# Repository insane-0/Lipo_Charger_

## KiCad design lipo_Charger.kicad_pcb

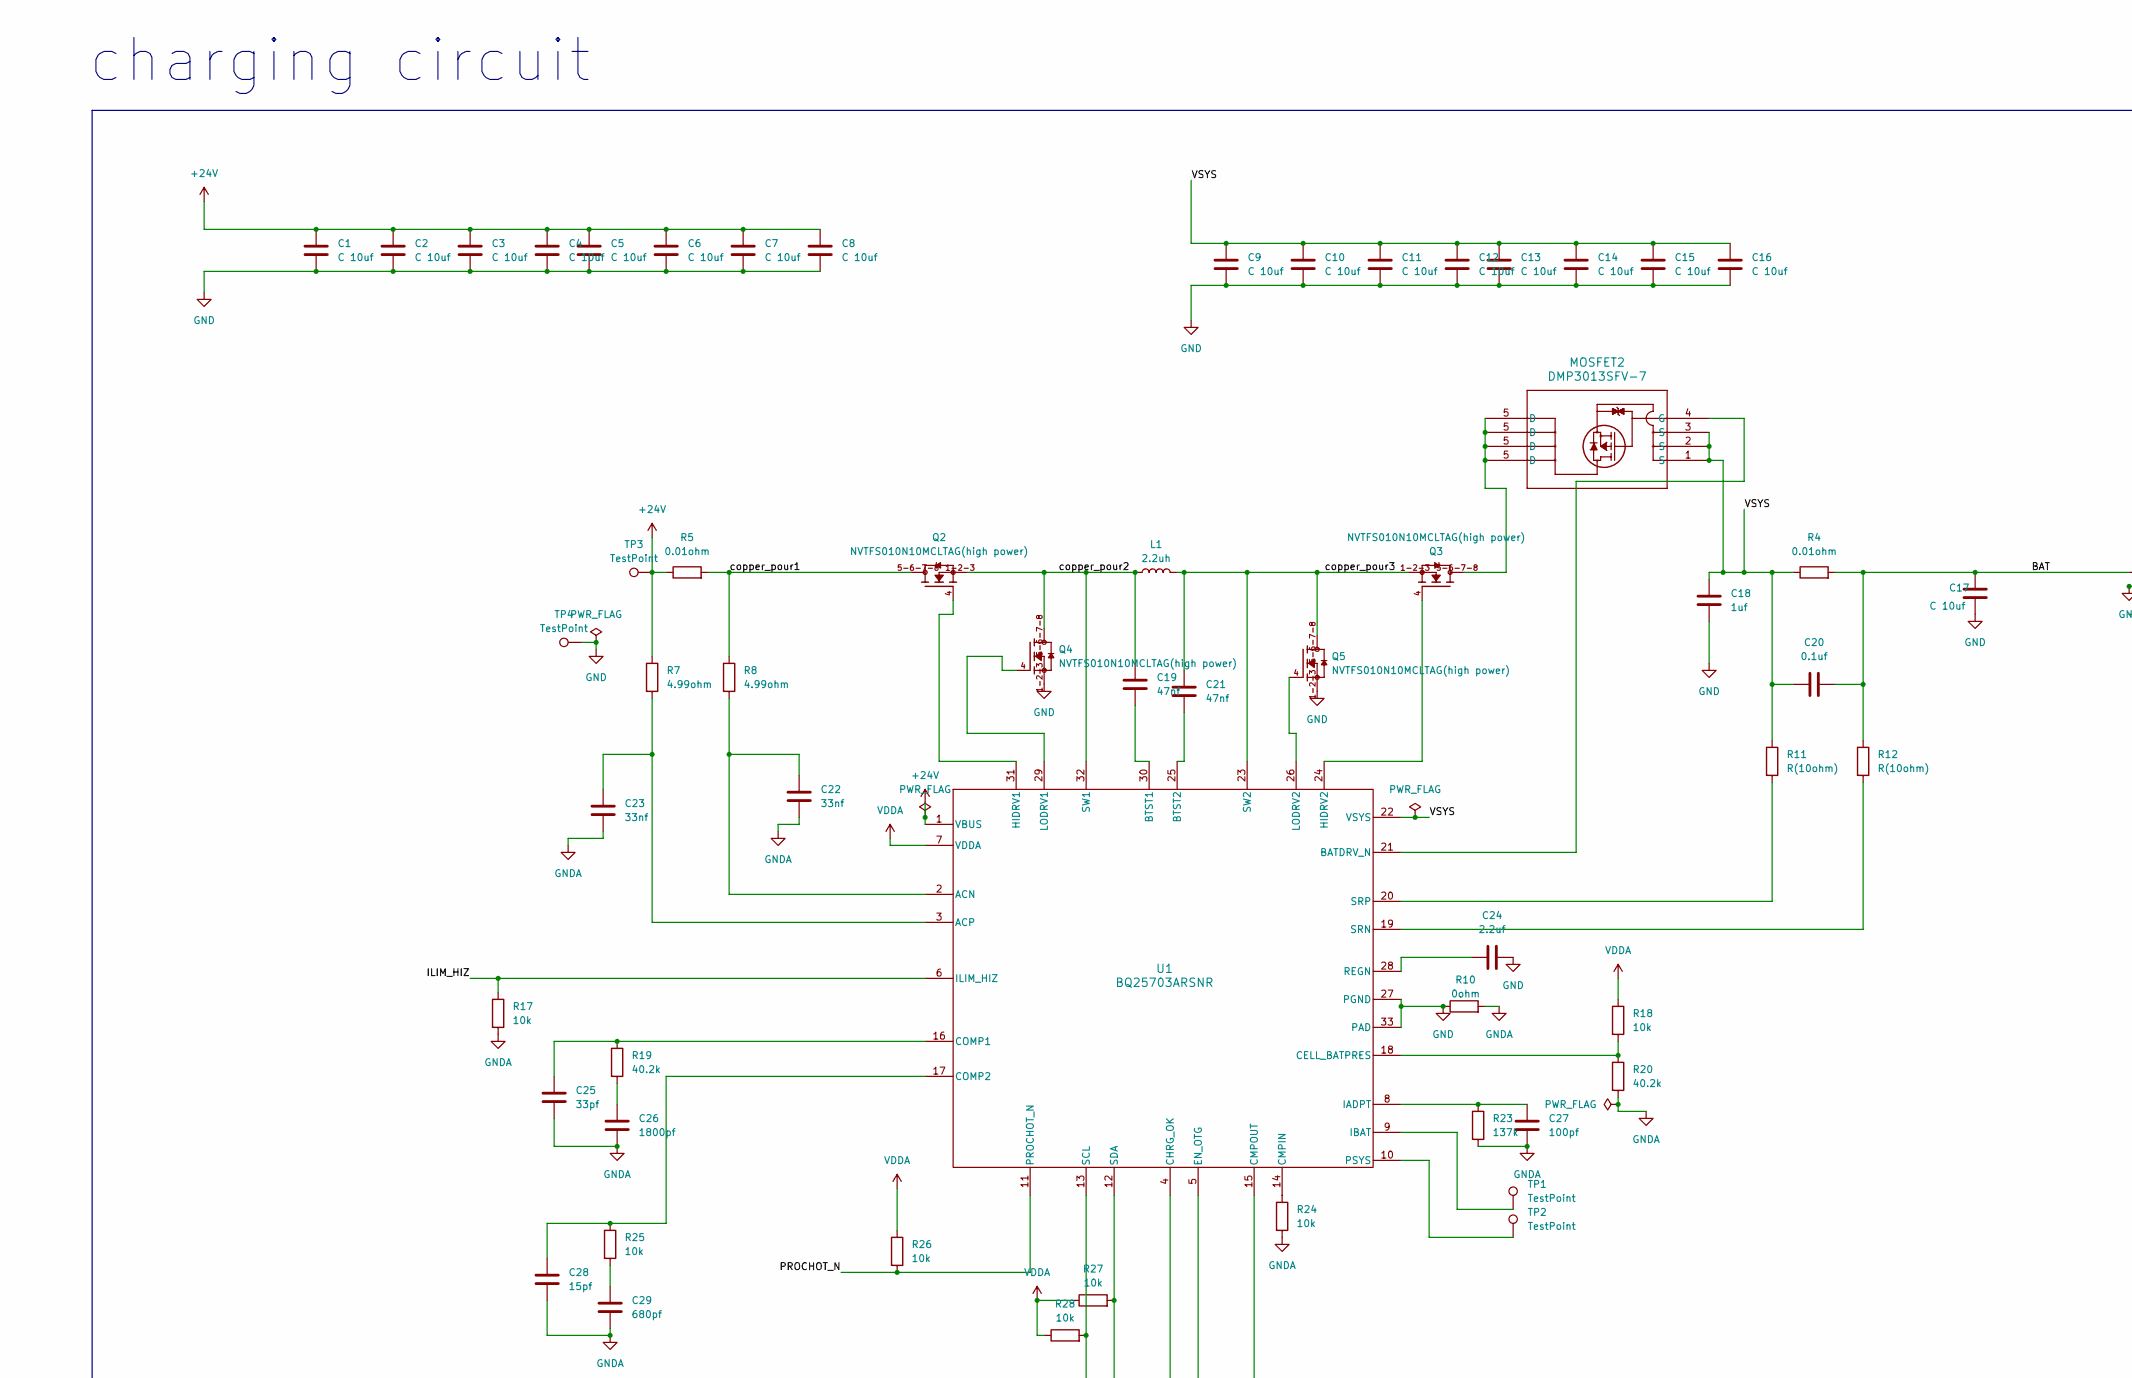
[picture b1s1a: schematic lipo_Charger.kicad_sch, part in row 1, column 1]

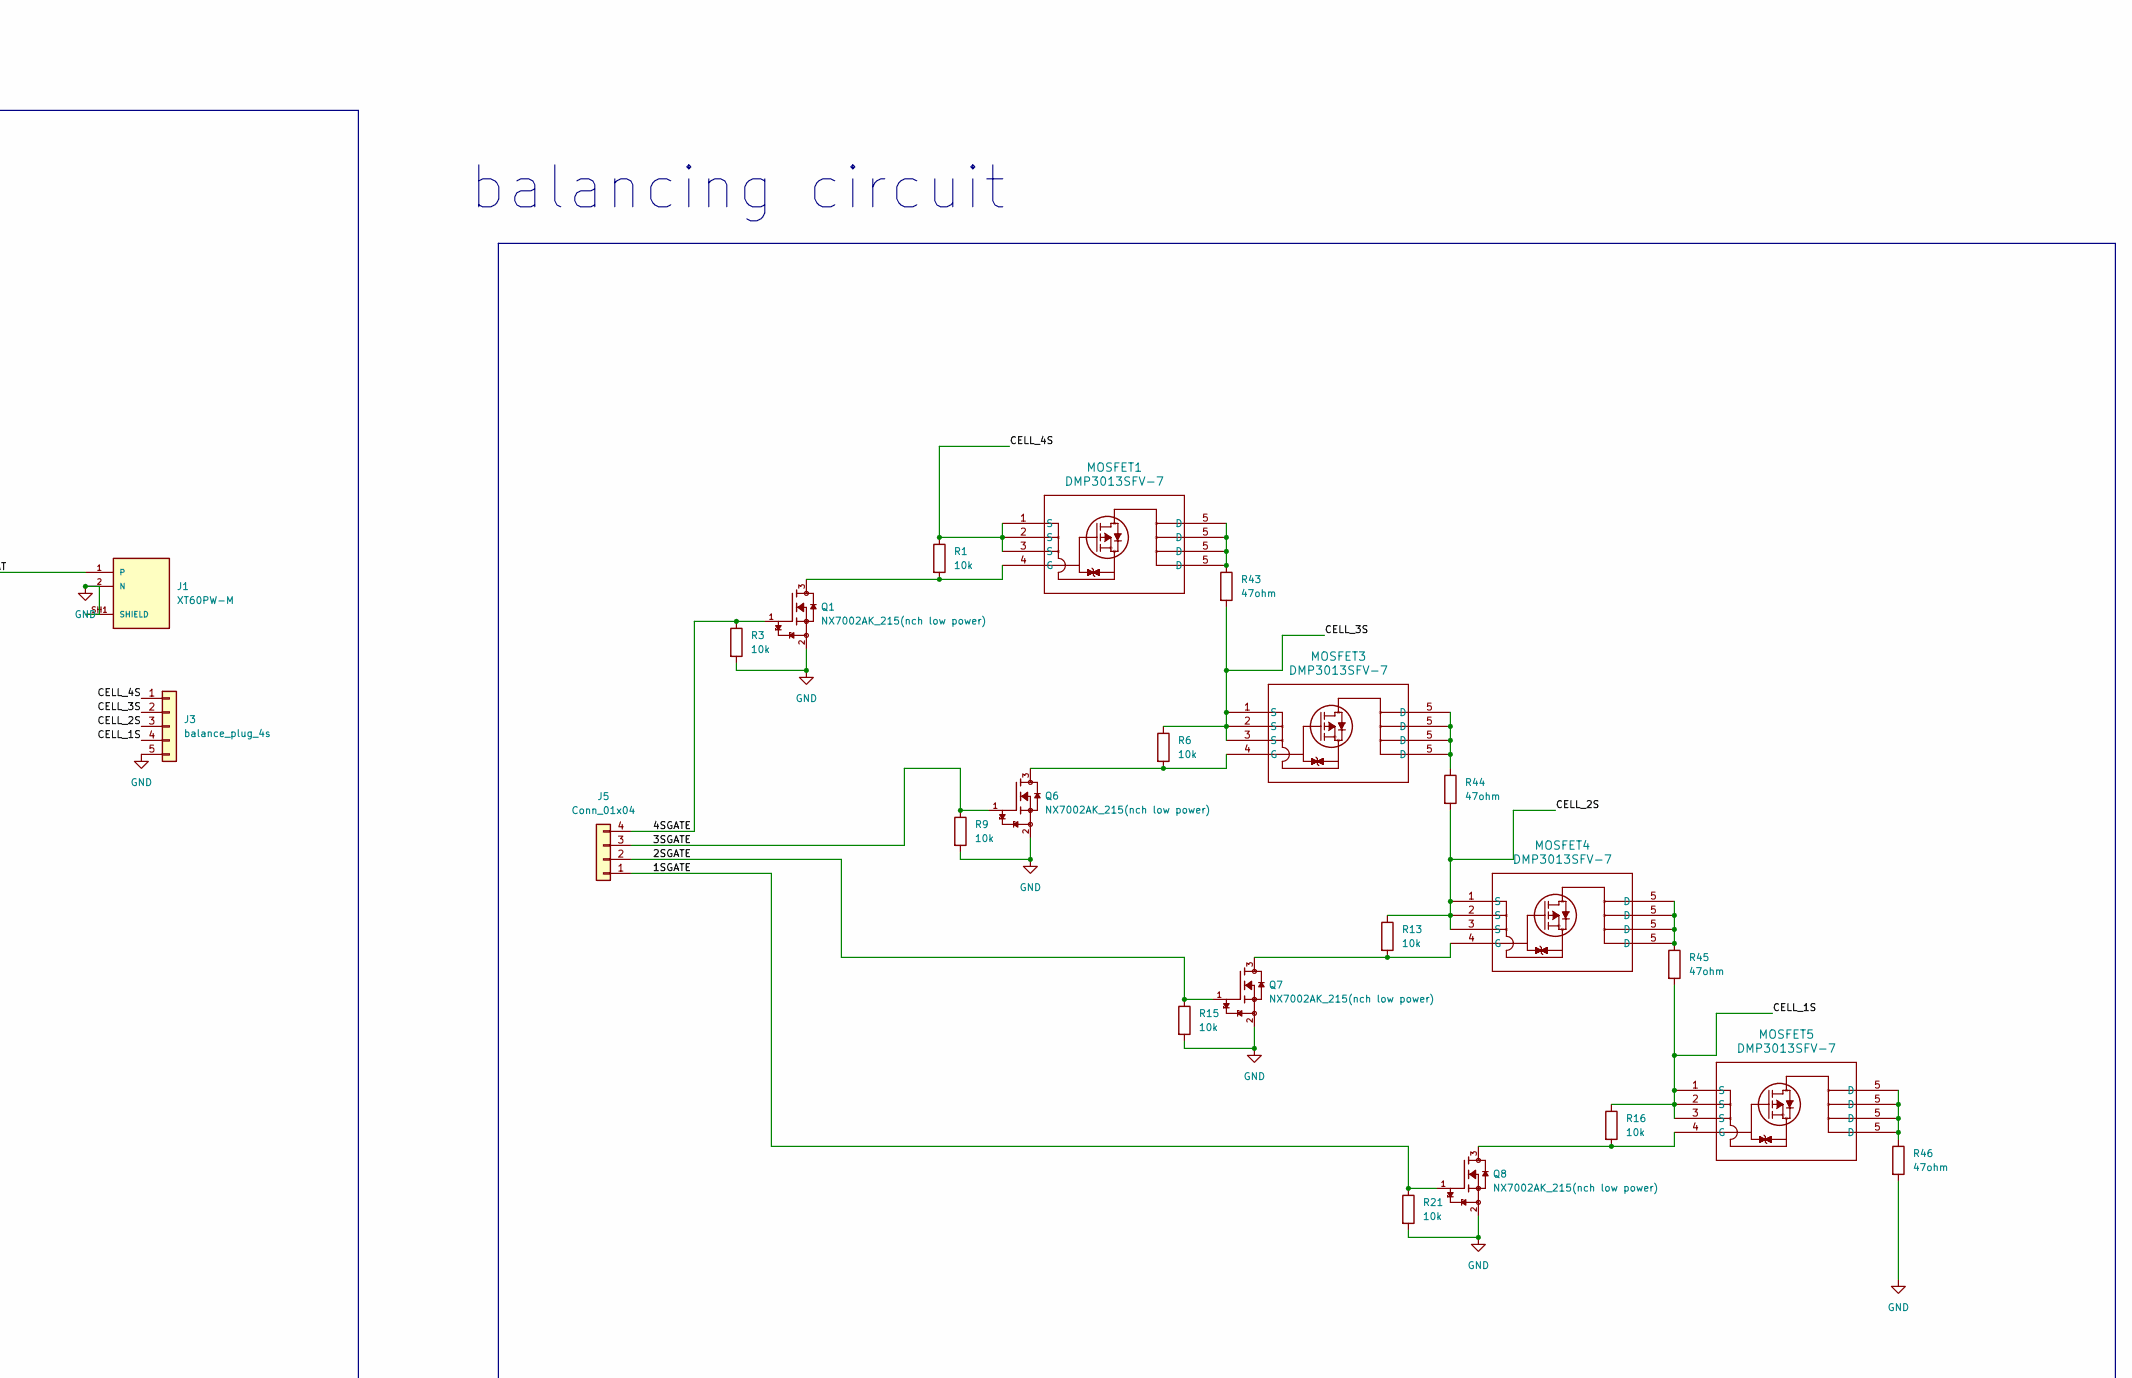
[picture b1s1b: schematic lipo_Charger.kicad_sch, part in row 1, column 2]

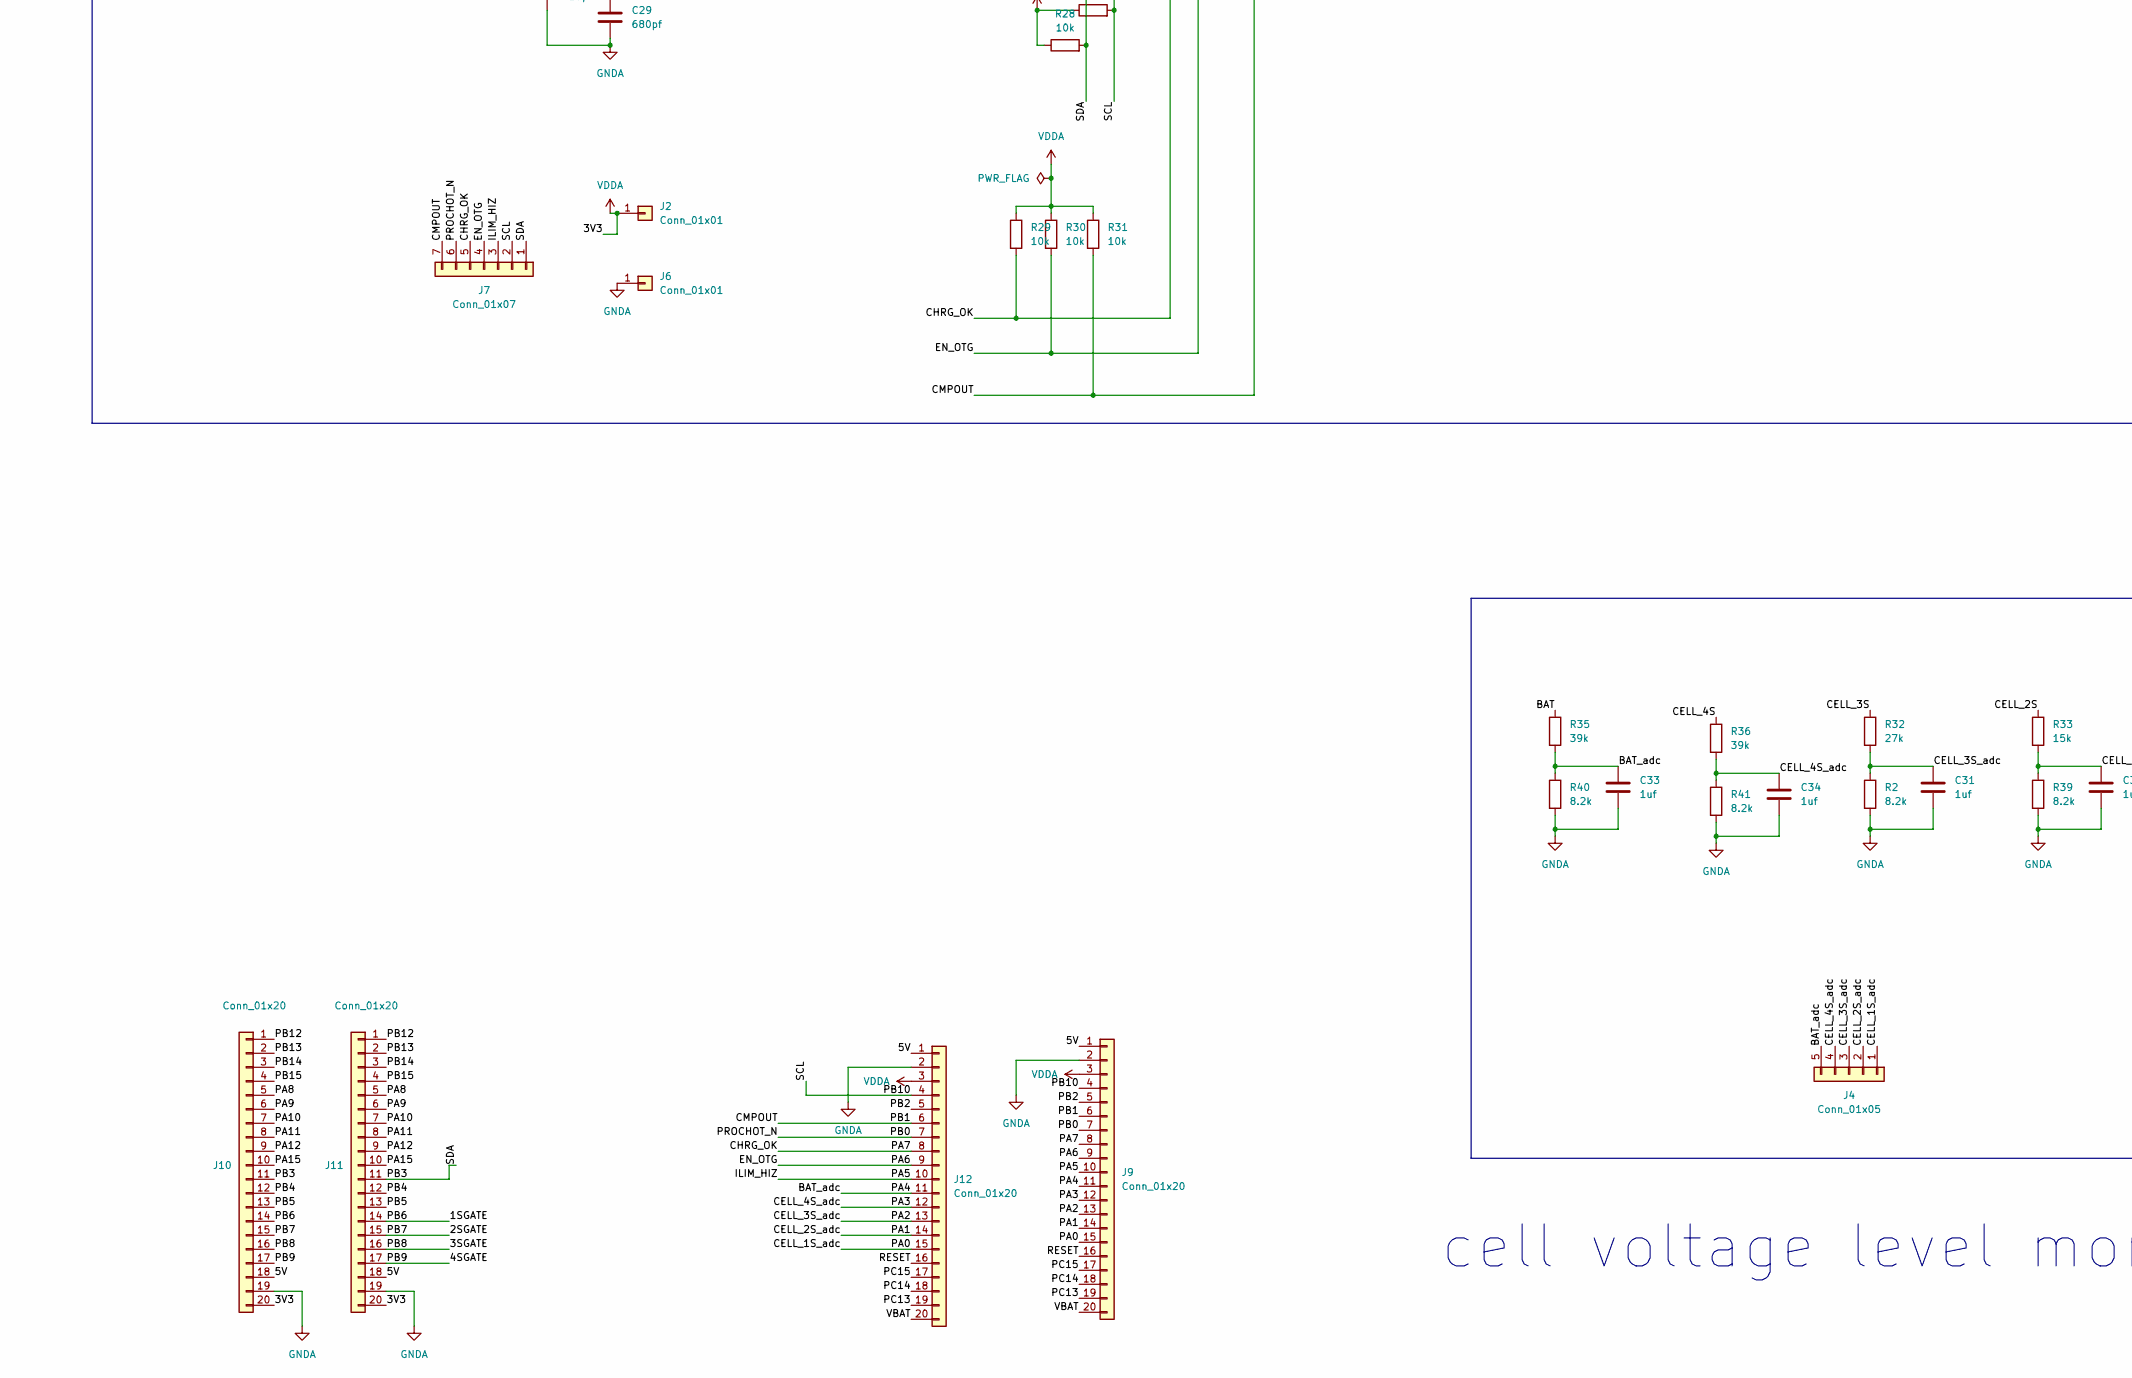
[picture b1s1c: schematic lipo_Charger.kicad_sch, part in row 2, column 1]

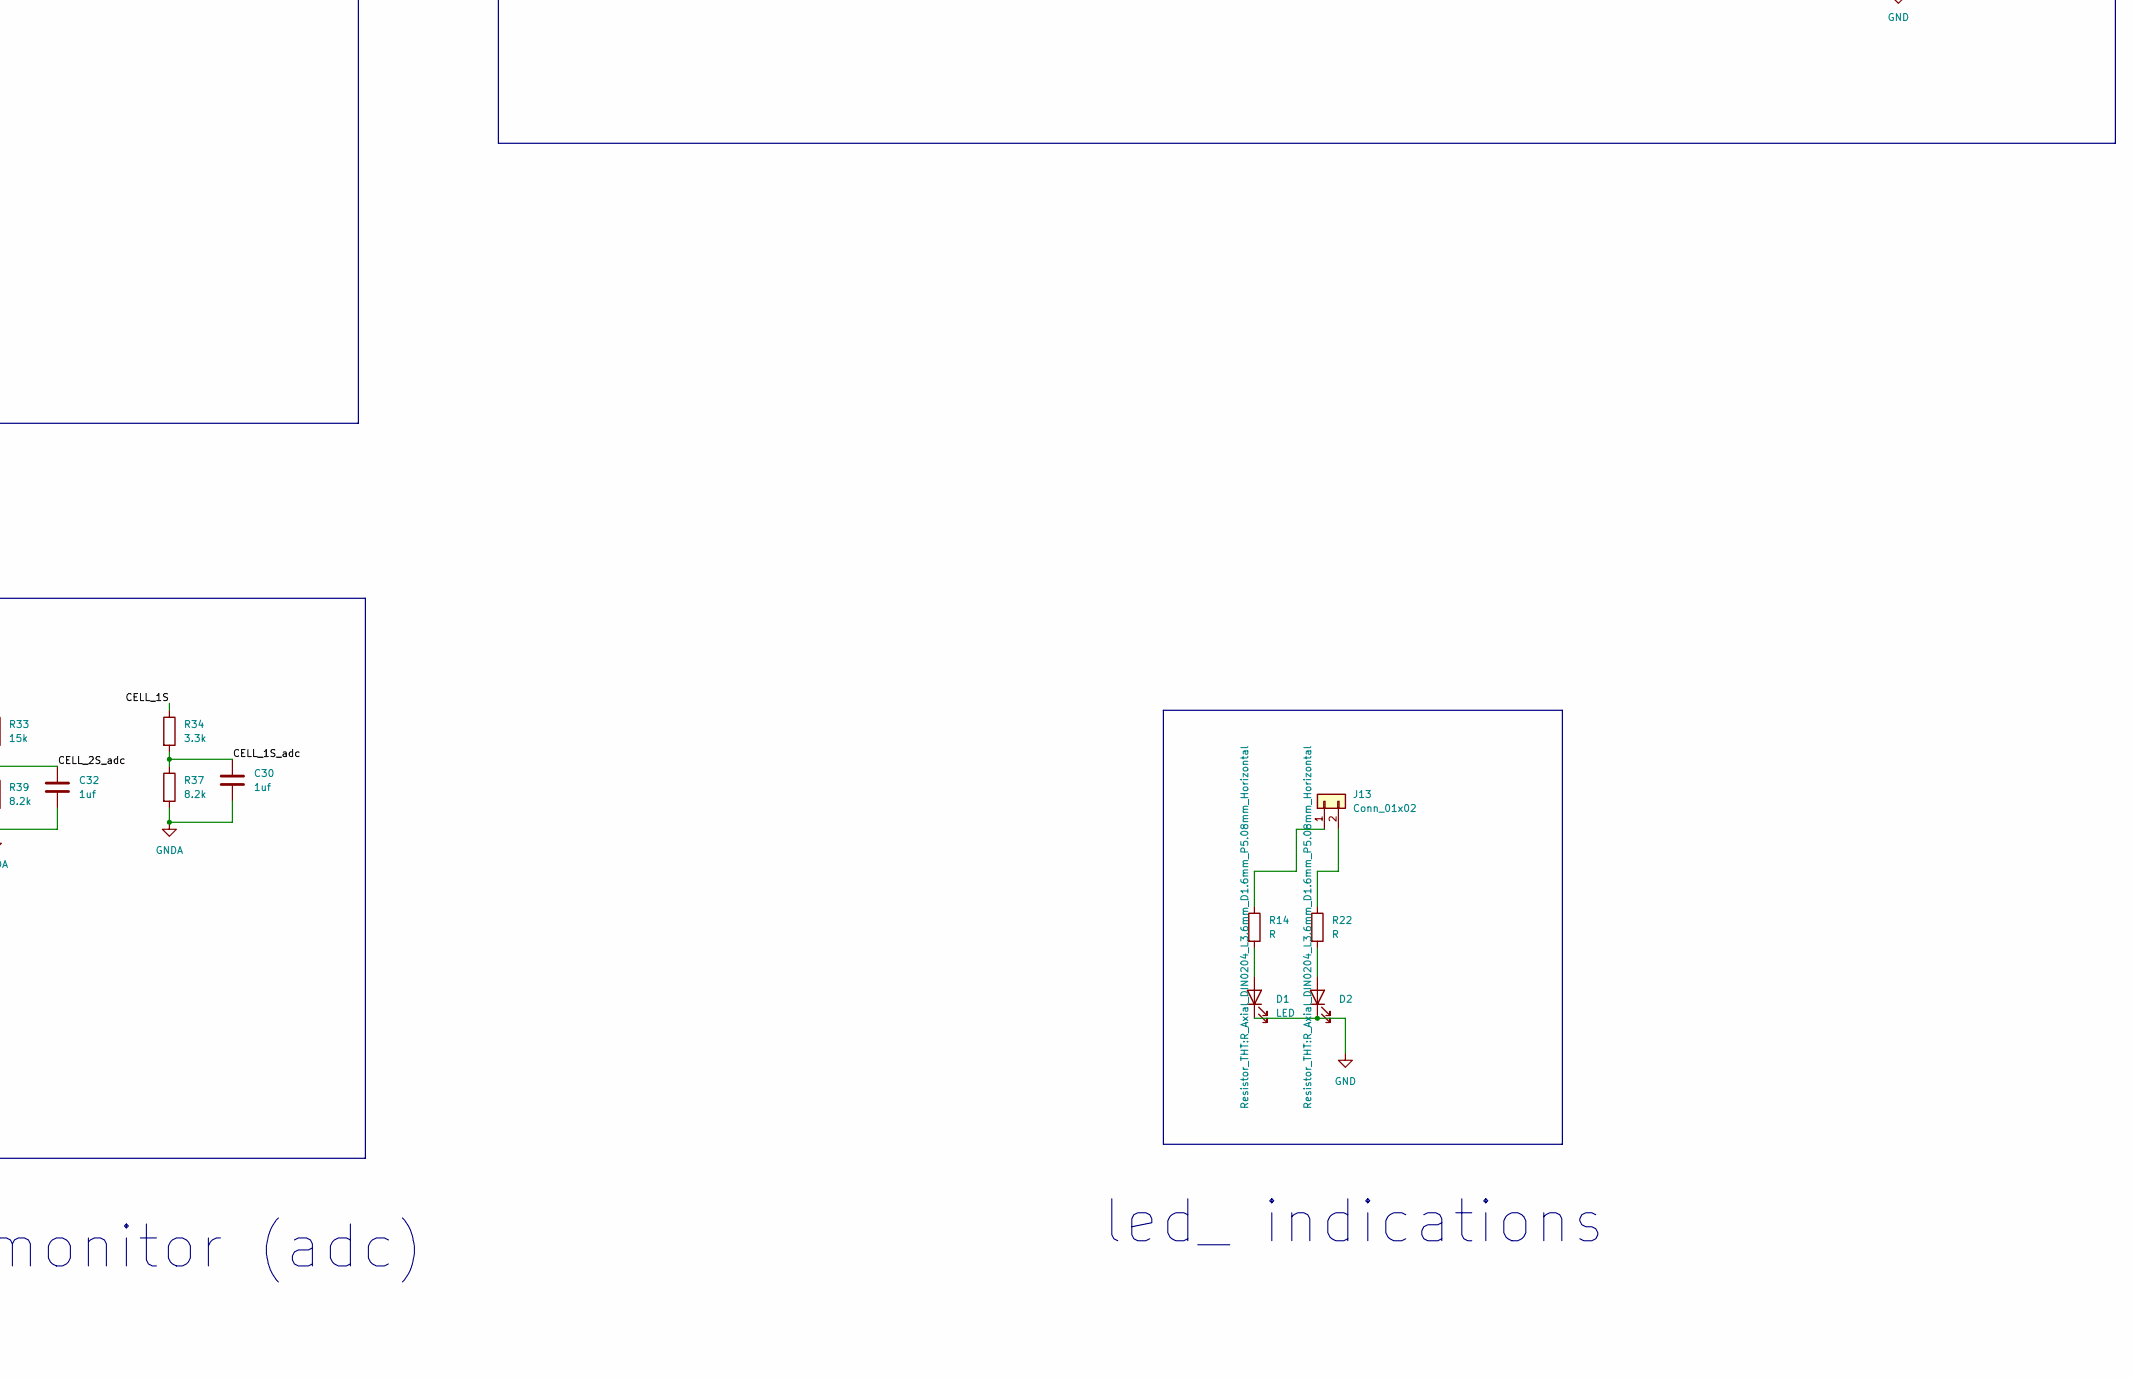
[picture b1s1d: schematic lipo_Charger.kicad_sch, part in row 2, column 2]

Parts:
C1, C2, C3, C4, C5, C6, C7, C8, C9, C10, C11, C12, C13, C14, C15, C16, C17: C 10uf; C_0805_2012Metric_Pad1.18x1.45mm_HandSolder
C18, C30, C31, C32, C33, C34: 1uf; C_0805_2012Metric_Pad1.18x1.45mm_HandSolder
C19, C21: 47nf; C_0603_1608Metric_Pad1.08x0.95mm_HandSolder
C20: 0.1uf; C_0603_1608Metric_Pad1.08x0.95mm_HandSolder
C22, C23: 33nf; C_0805_2012Metric_Pad1.18x1.45mm_HandSolder
C24: 2.2uf; D_1206_3216Metric_Pad1.42x1.75mm_HandSolder
C25: 33pf; C_0805_2012Metric_Pad1.18x1.45mm_HandSolder
C26: 1800pf; D_0805_2012Metric_Pad1.15x1.40mm_HandSolder
C27: 100pf; C_0603_1608Metric_Pad1.08x0.95mm_HandSolder
C28: 15pf; C_0402_1005Metric_Pad0.74x0.62mm_HandSolder
C29: 680pf; C_0603_1608Metric_Pad1.08x0.95mm_HandSolder
D1, D2: LED; LED_D5.0mm
J1: XT60PW-M; AMASS_XT60PW-M; PARTREV 1.2
J2, J6: Conn_01x01; PinHeader_1x01_P2.54mm_Vertical
J3: balance_plug_4s; JST_XH_B5B-XH-A_1x05_P2.50mm_Vertical
J4: Conn_01x05; PinHeader_1x05_P2.54mm_Vertical
J5: Conn_01x04; PinHeader_1x04_P2.54mm_Vertical
J7: Conn_01x07; PinHeader_1x07_P2.54mm_Vertical
J9, J10, J11, J12: Conn_01x20; PinHeader_1x20_P2.54mm_Vertical
J13: Conn_01x02; PinHeader_1x02_P2.54mm_Vertical
L1: 2.2uh; L_10.4x10.4_H4.8
MOSFET1, MOSFET2, MOSFET3, MOSFET4, MOSFET5: DMP3013SFV-7; POWERDI3333-8_UX_DIO-M
Q1, Q6, Q7, Q8: NX7002AK_215(nch low power); SOT95P230X110-3N(nch low power); PARTREV 7
Q2, Q3, Q4, Q5: NVTFS010N10MCLTAG(high power); TRANS_NVTFS010N10MCLTAG(nch high power); PARTREV 2
R1, R3, R6, R9, R13, R15, R16, R17, R18, R21, R24, R25, R26, R27, R28, R29, R30, R31: 10k; L_0805_2012Metric_Pad1.05x1.20mm_HandSolder
R2, R37, R39, R40, R41: 8.2k; R_0603_1608Metric_Pad0.98x0.95mm_HandSolder
R4, R5: 0.01ohm; R_2512_6332Metric_Pad1.40x3.35mm_HandSolder
R7, R8: 4.99ohm; L_0805_2012Metric_Pad1.05x1.20mm_HandSolder
R10: 0ohm; R_0603_1608Metric_Pad0.98x0.95mm_HandSolder
R11, R12: R(10ohm); R_0603_1608Metric_Pad0.98x0.95mm_HandSolder
R14, R22: R; R_Axial_DIN0204_L3.6mm_D1.6mm_P5.08mm_Horizontal
R19, R20: 40.2k; R_0603_1608Metric_Pad0.98x0.95mm_HandSolder
R23: 137k; R_0402_1005Metric_Pad0.72x0.64mm_HandSolder
R32: 27k; R_0603_1608Metric_Pad0.98x0.95mm_HandSolder
R33: 15k; R_0603_1608Metric_Pad0.98x0.95mm_HandSolder
R34: 3.3k; R_0603_1608Metric_Pad0.98x0.95mm_HandSolder
R35, R36: 39k; R_0603_1608Metric_Pad0.98x0.95mm_HandSolder
R43, R44, R45, R46: 47ohm; R_2512_6332Metric_Pad1.40x3.35mm_HandSolder
TP1, TP2: TestPoint; TestPoint_Pad_2.0x2.0mm
TP3, TP4: TestPoint; TestPoint_THTPad_4.0x4.0mm_Drill2.0mm
U1: BQ25703ARSNR; RSN0032B(1)

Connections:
+24V: C1.1, C2.1, C3.1, C4.1, C5.1, C6.1, C7.1, C8.1, R5.1, R7.1, TP3.1, U1.1 (VBUS)
/1SGATE: J5.1, J10.14, J11.14, Q8.1, R21.1
/2SGATE: J5.2, J10.15, J11.15, Q7.1, R15.1
/3SGATE: J5.3, J10.16, J11.16, Q6.1, R9.1
/4SGATE: J5.4, J10.17, J11.17, Q1.1, R3.1
/5V: J9.1, J10.18, J11.18, J12.1
/BAT: C17.1, C20.2, J1.1, R4.2, R12.1, R35.1
/BAT_adc: C33.2, J4.5, J9.11, J12.11, R35.2, R40.1
/CELL_1S: J3.4, MOSFET5.1 (S), MOSFET5.2 (S), MOSFET5.3 (S), R16.1, R34.1, R45.2
/CELL_1S_adc: C30.2, J4.1, J9.15, J12.15, R34.2, R37.1
/CELL_2S: J3.3, MOSFET4.1 (S), MOSFET4.2 (S), MOSFET4.3 (S), R13.1, R33.1, R44.2
/CELL_2S_adc: C32.2, J4.2, J9.14, J12.14, R33.2, R39.1
/CELL_3S: J3.2, MOSFET3.1 (S), MOSFET3.2 (S), MOSFET3.3 (S), R6.1, R32.1, R43.2
/CELL_3S_adc: C31.2, J4.3, J9.13, J12.13, R2.1, R32.2
/CELL_4S: J3.1, MOSFET1.1 (S), MOSFET1.2 (S), MOSFET1.3 (S), R1.1, R36.1
/CELL_4S_adc: C34.2, J4.4, J9.12, J12.12, R36.2, R41.1
/CHRG_OK: J7.5, J9.8, J12.8, R29.2, U1.4 (CHRG_OK)
/CMPOUT: J7.7, J9.6, J12.6, R31.2, U1.15 (CMPOUT)
/EN_OTG: J7.4, J9.9, J12.9, R30.2, U1.5 (EN_OTG)
/ILIM_HIZ: J7.3, J9.10, J12.10, R17.1, U1.6 (ILIM_HIZ)
/PA8: J10.5, J11.5
/PA9: J10.6, J11.6
/PA10: J10.7, J11.7
/PA11: J10.8, J11.8
/PA12: J10.9, J11.9
/PA15: J10.10, J11.10
/PB0: J7.6, J9.7, J12.7, R26.2, U1.11 (PROCHOT_N)
/PB2: J9.5, J12.5
/PB3: J7.1, J10.11, J11.11, R28.2, U1.13 (SCL)
/PB4: J10.12, J11.12
/PB5: J10.13, J11.13
/PB10: J7.2, J9.4, J12.4, R27.2, U1.12 (SDA)
/PB12: J10.1, J11.1
/PB13: J10.2, J11.2
/PB14: J10.3, J11.3
/PB15: J10.4, J11.4
/PC13: J9.19, J12.19
/PC14: J9.18, J12.18
/PC15: J9.17, J12.17
/RESET: J9.16, J12.16
/VBAT: J9.20, J12.20
/VSYS: C9.1, C10.1, C11.1, C12.1, C13.1, C14.1, C15.1, C16.1, C18.1, C20.1, MOSFET2.1 (S), MOSFET2.2 (S), MOSFET2.3 (S), R4.1, R11.1, U1.22 (VSYS)
/copper_pour1: Q2.5-6-7-8, R5.2, R8.1
/copper_pour2: C19.1, L1.1, Q2.1-2-3, Q4.5-6-7-8, U1.32 (SW1)
/copper_pour3: C21.1, L1.2, Q3.1-2-3, Q5.5-6-7-8, U1.23 (SW2)
GND: C1.2, C2.2, C3.2, C4.2, C5.2, C6.2, C7.2, C8.2, C9.2, C10.2, C11.2, C12.2, C13.2, C14.2, C15.2, C16.2, C17.2, C18.2, C24.2, D1.1 (K), D2.1 (K), J1.2 (N), J1.SH1 (SHIELD), J1.SH2 (SHIELD), J3.5, Q1.2, Q4.1-2-3, Q5.1-2-3, Q6.2, Q7.2, Q8.2, R3.2, R9.2, R10.1, R15.2, R21.2, R46.2, TP4.1, U1.27 (PGND), U1.33 (PAD)
GNDA: C22.2, C23.2, C25.2, C26.2, C27.2, C28.2, C29.2, C30.1, C31.1, C32.1, C33.1, C34.1, J6.1, J9.2, J10.19, J11.19, J12.2, R2.2, R10.2, R17.2, R20.2, R23.2, R24.2, R37.2, R39.2, R40.2, R41.2
unnamed: C26.1, R19.2
unnamed: C29.1, R25.2
unnamed: D1.2 (A), R14.2
unnamed: D2.2 (A), R22.2
unnamed: J13.1, R14.1
unnamed: J13.2, R22.1
unnamed: MOSFET1.5 (D), R43.1
unnamed: MOSFET1.4 (G), Q1.3, R1.2
unnamed: MOSFET2.5 (D), Q3.5-6-7-8
unnamed: MOSFET2.4 (G), U1.21 (BATDRV_N)
unnamed: MOSFET3.5 (D), R44.1
unnamed: MOSFET3.4 (G), Q6.3, R6.2
unnamed: MOSFET4.5 (D), R45.1
unnamed: MOSFET4.4 (G), Q7.3, R13.2
unnamed: MOSFET5.5 (D), R46.1
unnamed: MOSFET5.4 (G), Q8.3, R16.2
unnamed: C22.1, R8.2, U1.2 (ACN)
unnamed: C23.1, R7.2, U1.3 (ACP)
unnamed: C19.2, U1.30 (BTST1)
unnamed: C21.2, U1.25 (BTST2)
unnamed: R18.2, R20.1, U1.18 (CELL_BATPRES)
unnamed: R24.1, U1.14 (CMPIN)
unnamed: C25.1, R19.1, U1.16 (COMP1)
unnamed: C28.1, R25.1, U1.17 (COMP2)
unnamed: Q2.4, U1.31 (HIDRV1)
unnamed: Q3.4, U1.24 (HIDRV2)
unnamed: C27.1, R23.1, U1.8 (IADPT)
unnamed: TP1.1, U1.9 (IBAT)
unnamed: Q4.4, U1.29 (LODRV1)
unnamed: Q5.4, U1.26 (LODRV2)
unnamed: TP2.1, U1.10 (PSYS)
unnamed: C24.1, U1.28 (REGN)
unnamed: R12.2, U1.19 (SRN)
unnamed: R11.2, U1.20 (SRP)
VDDA: J2.1, J9.3, J10.20, J11.20, J12.3, R18.1, R26.1, R27.1, R28.1, R29.1, R30.1, R31.1, U1.7 (VDDA)

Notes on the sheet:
balancing circuit
cell voltage level monitor (adc)
charging circuit
led_ indications

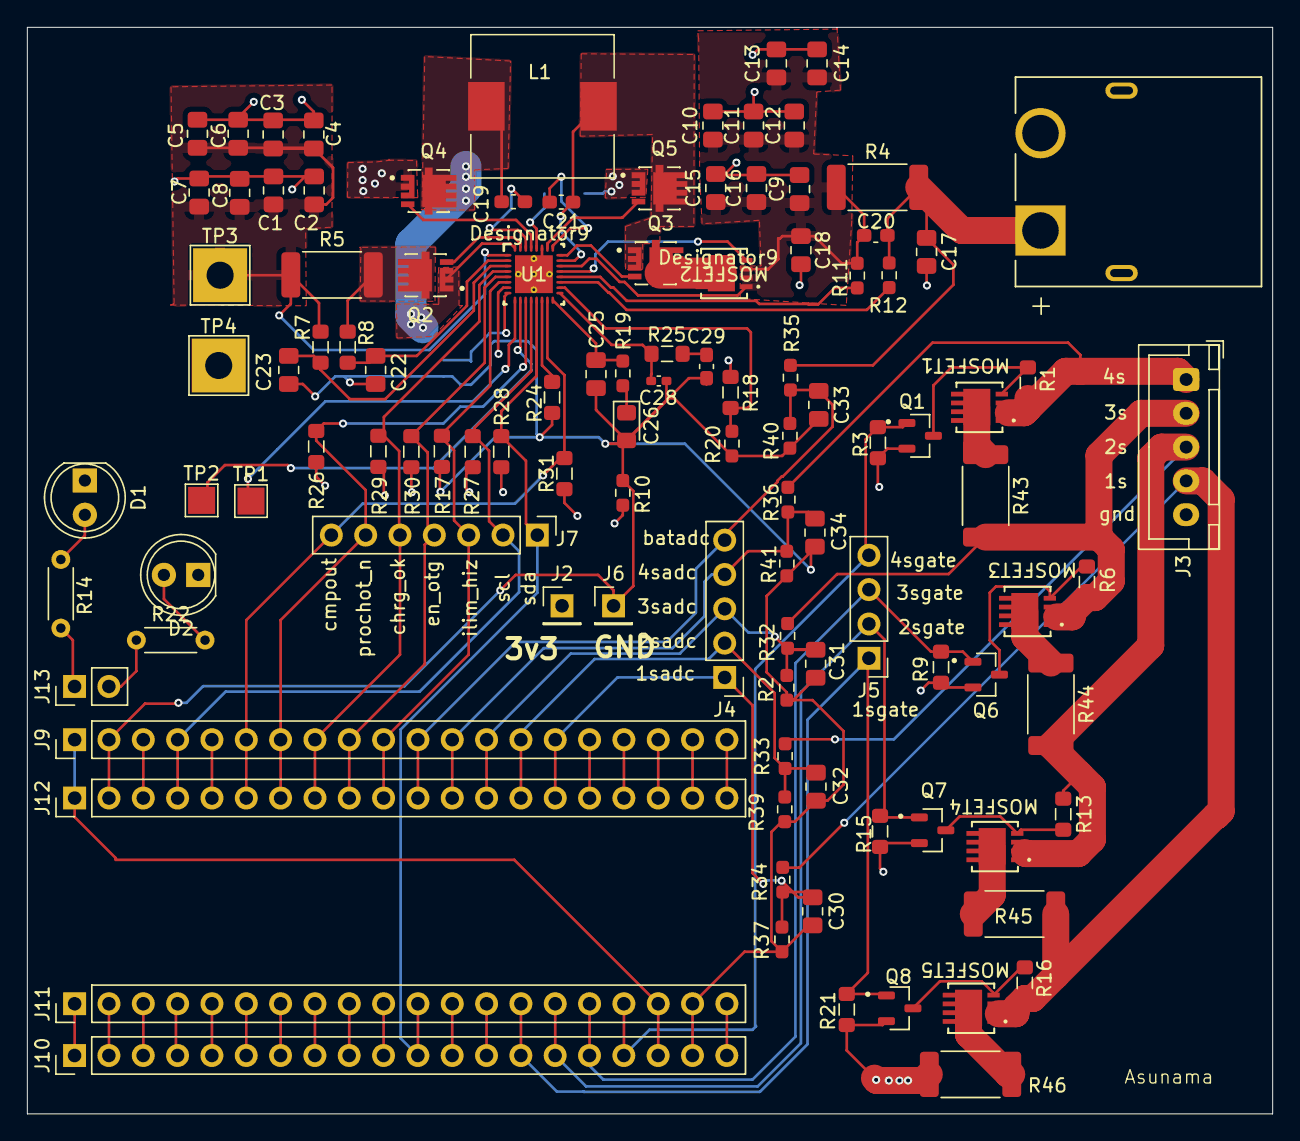
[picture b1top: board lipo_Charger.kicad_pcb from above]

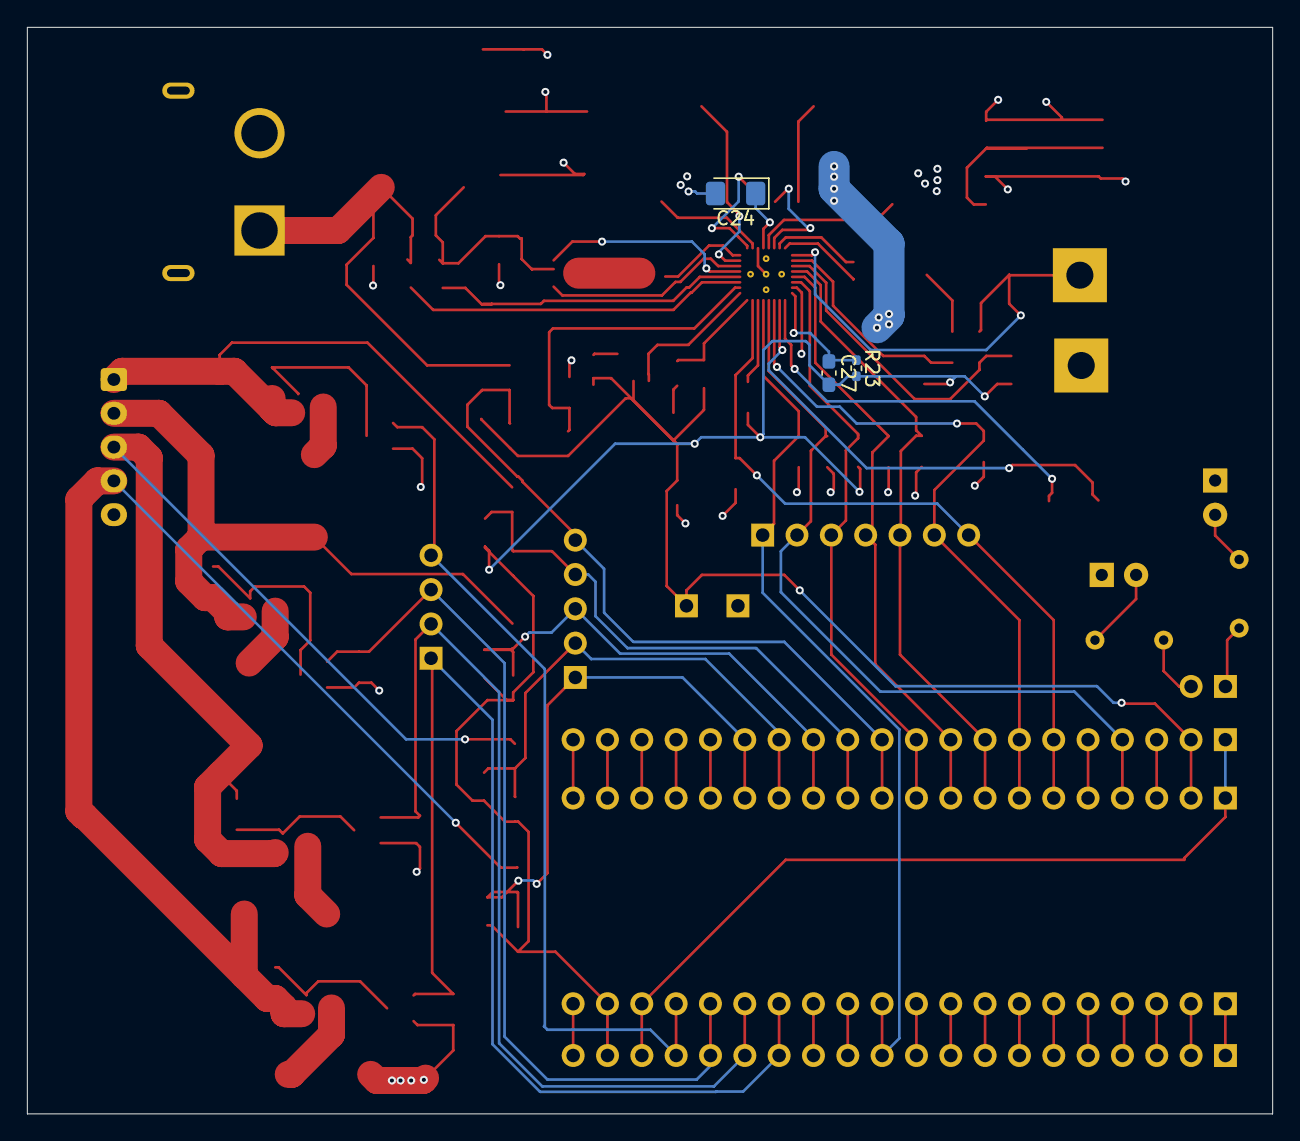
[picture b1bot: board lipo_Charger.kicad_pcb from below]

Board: 4 copper layers, 92.1 x 80.4 mm, 111 parts (3 on the bottom side), 82 nets.

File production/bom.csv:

Designator,Footprint,Quantity,Value,LCSC Part #
"C1, C10, C11, C12, C13, C14, C15, C16, C17, C2, C3, C4, C5, C6, C7, C8, C9",0805,17,C 10uf,https://robu.in/product/10uf-10000nf-50v-capacitor-0805-smd-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
"C18, C30, C31, C32, C33, C34",0805,6,1uf,https://robu.in/product/1uf-1000nf-50v-capacitor-0805-smd-pa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
"C19, C21",0603,2,47nf,https://robu.in/product/47nf-50v-capacitor-0603-smd-package-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
C20,0603,1,0.1uf,https://robu.in/product/0-1uf-capacitor-smdc-0603/
"C22, C23",0805,2,33nf,https://robu.in/product/33nf-0805-surface-mount-multilayer-c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
C24,1206,1,2.2uf,https://robu.in/product/cs3216x7r225k500nri-samwha-50v-2-2uf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
C25,0805,1,33pf,https://robu.in/product/33pf-0603-surface-mount-multilayer-c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
C26,0805,1,1800pf,https://robu.in/product/1-8nf-1800pf-50v-capacitor-0805-smd-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
C27,0603,1,100pf,https://robu.in/product/100pf-0603-surface-mount-multilayer-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
C28,0402,1,15pf,https://robu.in/product/gjm1555c1h150fb01d-murata-electronic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
C29,0603,1,680pf,https://robu.in/product/680pf-0-68nf-50v-capacitor-0603-smd-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
"D1, D2",LED_D5.0mm,2,LED,
J1,AMASS_XT60PW-M,1,XT60PW-M,https://robu.in/product/amass-xt60pw30-male-connector-xt60pw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
"J10, J11, J12, J9",PinHeader_1x20_P2.54mm_Vertical,4,Conn_01x20,
J13,PinHeader_1x02_P2.54mm_Vertical,1,Conn_01x02,
"J2, J6",PinHeader_1x01_P2.54mm_Vertical,2,Conn_01x01,
J3,JST_XH_B5B-XH-A_1x05_P2.50mm_Vertical,1,balance_plug_4s,https://roboticsdna.in/product/5-pin-jst-male-female-pair-co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
J4,PinHeader_1x05_P2.54mm_Vertical,1,Conn_01x05,
J5,PinHeader_1x04_P2.54mm_Vertical,1,Conn_01x04,
J7,PinHeader_1x07_P2.54mm_Vertical,1,Conn_01x07,
L1,L_10.4x10.4_H4.8,1,2.2uh,https://robu.in/product/cdrh104r-2-2%CE%BCh-power-inductor-p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
"MOSFET1, MOSFET2, MOSFET3, MOSFET4, MOSFET5",POWERDI3333-8_UX_DIO-M,5,DMP3013SFV-7,https://robu.in/product/dmp3013sfv-hxy-mosfet-30v-55a-1-p-ch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
"Q1, Q6, Q7, Q8",SOT95P230X110-3N(nch low power),4,NX7002AK_215(nch low power),https://robu.in/product/nx7002akar-nexperia-nx7002akar-power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
"Q2, Q3, Q4, Q5",TRANS_NVTFS010N10MCLTAG(nch high power),4,NVTFS010N10MCLTAG(high power),https://robu.in/product/nvtfs008n04c-hxy-mosfet-40v-60a-1-n-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
"R1, R13, R15, R16, R17, R18, R21, R24, R25, R26, R27, R28, R29, R3, R30, R31, R6, R9",0805,18,10k,https://roboticsdna.in/product/10k%cf%89-thick-film-smd-resi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
R10,0603,1,0ohm,
"R11, R12",0603,2,R(10ohm),https://robu.in/product/rc0603fr-0710rl-yageo-smd-chip-resis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
"R14, R22",R_Axial_DIN0204_L3.6mm_D1.6mm_P5.08mm_Horizontal,2,R,
"R19, R20",0603,2,40.2k,https://robu.in/product/ac0603fr-0740k2l-yageo-res-thick-fil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
"R2, R37, R39, R40, R41",0603,5,8.2k,https://robu.in/product/rc0603fr-078k2l-yageo-res-thick-film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
R23,0402,1,137k,https://robu.in/product/ac0402fr-07137kl-yageo-res-thick-fil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
R32,0603,1,27k,https://robu.in/product/ac0603fr-0727kl-yageo-res-thick-film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
R33,0603,1,15k,https://robu.in/product/ac0603fr-0715kl-yageo-res-thick-film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
R34,0603,1,3.3k,https://robu.in/product/3-3k-ohm-1-4w-0603-surface-mount-chi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
"R35, R36",0603,2,39k,https://robu.in/product/ac0603fr-0739kl-yageo-res-thick-film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
"R4, R5",2512,2,0.01ohm,https://robu.in/product/0-01-ohm-3w-surface-mount-sense-resi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
"R43, R44, R45, R46",2512,4,47ohm,https://robu.in/product/rc2512jk-0747rl-yageo-smd-chip-resis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
"R7, R8",0805,2,4.99ohm,https://robu.in/product/rc0805fr-074r99l-yageo-smd-chip-resi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
"TP1, TP2",TestPoint_Pad_2.0x2.0mm,2,TestPoint,
"TP3, TP4",TestPoint_THTPad_4.0x4.0mm_Drill2.0mm,2,TestPoint,
U1,RSN0032B(1),1,BQ25703ARSNR,https://robu.in/product/bq25713rsnr-texas-instruments-3-5v24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

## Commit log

2026-02-27 progress 1
2026-03-01 progress overall sch for the ti ic has done now need to get the actual comp and then update it
2026-03-01 some changes made
2026-03-01 current sensing pins have connected the req components
2026-03-02 bom generated need to assign footprints and review the sch add balancing and mcu circuit
2026-03-02 bom updated
2026-03-04 symbol added to the library and footprint assigned mosfets are yet to be added
2026-03-06 three r one c balancing circuit dev board has to be done yet
2026-03-07 adcc has to be done stm dev board if needed has to be inccluded
2026-03-07 need to checked sch and then routing thickness has to be calculated and ground fill has to be added
2026-03-07 need to add stm dev boarrd and silkscreen managing sch rechecik and trace width check eed to add gnd and power plane
2026-03-11 need to seperate analog and digital ground and reroute everything
2026-03-14 all the links of the components has been assigned in the library for routing components placement is optimizes need routing
2026-03-15 power side routing is done need to look into where i switch layers balancing side and interection with stm has to be done
2026-03-17 done everything need to check before ordering once
2026-03-17 silk screen labelling done for headers
2026-03-17 silk screen arrangement pushing again
2026-03-17 sch organized a bit
2026-03-19 xt60 conenector was in the wrong direction now resolved all the footprints has been verfied by cross checking the components bought balance plug not yet got in hand that has to be checcked
2026-03-19 copper pour mismatch due to some glitches rectified it no erc error
2026-03-19 final correction has been ready to order
2026-03-26 final ordered file
2026-04-22 Add datasheets and update Lipo Charger footprints
